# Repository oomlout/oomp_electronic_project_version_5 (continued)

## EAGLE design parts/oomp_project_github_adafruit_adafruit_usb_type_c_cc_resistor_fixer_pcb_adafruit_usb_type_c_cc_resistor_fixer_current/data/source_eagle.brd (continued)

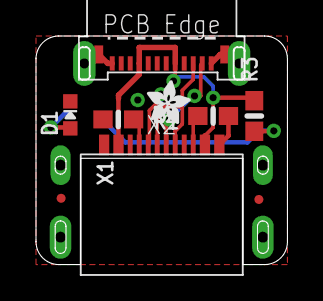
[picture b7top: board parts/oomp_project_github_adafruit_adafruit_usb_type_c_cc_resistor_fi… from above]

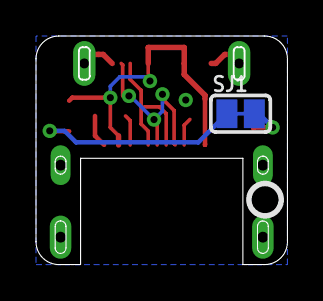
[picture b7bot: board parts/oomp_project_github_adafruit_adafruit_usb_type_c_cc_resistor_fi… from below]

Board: 2 copper layers, 14.0 x 12.7 mm, 14 parts (3 on the bottom side), 8 nets.

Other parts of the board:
PLABEL0: PLABEL0
PLABEL1: PLABEL1
PLABEL2: PLABEL2
U$3: ADAFRUIT_2.5MM
U$8: PCBFEAT-REV-040

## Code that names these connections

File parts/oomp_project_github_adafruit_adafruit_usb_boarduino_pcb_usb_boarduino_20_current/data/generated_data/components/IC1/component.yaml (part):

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    dnp: false
    pins:
    - number: '1'
      name: PC6(/RESET/PCI14)
      electrical_type: bidirectional
      graphic_style: inverted
      local_position:
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        pin_number: A'
        pin_name: P1
    - number: '2'
      name: (PCI16/RXD)PD0
      electrical_type: bidirectional
      graphic_style: line
      local_position:
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        pin_number: '1'
        pin_name: '1'
    - number: '3'
      name: (PCI17/TXD)PD1
      electrical_type: bidirectional
      graphic_style: line
      local_position:
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        pin_number: '2'
        pin_name: '2'
    - number: '4'
      name: (PCI18/INT0)PD2
      electrical_type: bidirectional
      graphic_style: line
      local_position:
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        pin_number: '3'
        pin_name: '3'
    - number: '5'
      name: (PCI19/INT1/OC2B)PD3
      electrical_type: bidirectional
      graphic_style: line
      local_position:
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        pin_number: '4'
        pin_name: '4'
    - number: '6'
      name: (PCI20/XCK/T0)PD4
      electrical_type: bidirectional
      graphic_style: line
      local_position:
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        pin_name: +
      - reference: IC1
        pin_number: '20'
        pin_name: AVCC
      - reference: IC2
        pin_number: '4'
        pin_name: VCCIO
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        pin_name: C
      - reference: IC1
        pin_number: '22'
        pin_name: AGND
      - reference: IC2
        pin_number: '7'
        pin_name: GND
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        pin_name: GND3
      - reference: IC2
        pin_number: '25'
        pin_name: AGND
      - reference: IC2
        pin_number: '26'
        pin_name: TEST
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        pin_number: GND
        pin_name: GND
    - number: '9'
      name: PB6(XTAL1/TOSC1/PCI6)
      electrical_type: bidirectional
      graphic_style: line
      local_position:
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        pin_number: P$2
        pin_name: P$2
    - number: '10'
      name: PB7(XTAL2/TOSC2/PCI7)
      electrical_type: bidirectional
      graphic_style: line
      local_position:
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        pin_number: P$1
        pin_name: P$1
    - number: '11'
      name: (PCI21/T1/OC0B)PD5
      electrical_type: bidirectional
      graphic_style: line
      local_position:
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        pin_number: '6'
        pin_name: '6'
    - number: '12'
      name: (PCI22/AIN0OC0A)PD6
      electrical_type: bidirectional
      graphic_style: line
      local_position:
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        pin_number: '7'
        pin_name: '7'
    - number: '13'
      name: (PCI23/AIN1)PD7
      electrical_type: bidirectional
      graphic_style: line
      local_position:
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        pin_number: '8'
        pin_name: '8'
    - number: '14'
      name: (PCI0/ICP/CLKO)PB0
      electrical_type: bidirectional
      graphic_style: line
      local_position:
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        pin_number: '1'
        pin_name: '1'
    - number: '15'
      name: (PCI1/OC1A/OC1S)PB1
      electrical_type: bidirectional
      graphic_style: line
      local_position:
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        pin_number: '2'
        pin_name: '2'
    - number: '16'
      name: (PCI2/SS/OC1B)PB2
      electrical_type: bidirectional
      graphic_style: line
      local_position:
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        pin_number: '3'
        pin_name: '3'
    - number: '17'
      name: (PCI3/MOSI/OC2A)PB3
      electrical_type: bidirectional
      graphic_style: line
      local_position:
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        pin_number: '4'
        pin_name: '4'
    - number: '18'
      name: (PCI4/MISO)PB4
      electrical_type: bidirectional
      graphic_style: line
      local_position:
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        pin_number: '1'
        pin_name: '1'
    - number: '19'
      name: (PCI5/SCK)PB5
      electrical_type: bidirectional
      graphic_style: line
      local_position:
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        pin_name: GND3
      - reference: IC2
        pin_number: '25'
        pin_name: AGND
      - reference: IC2
        pin_number: '26'
        pin_name: TEST
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        pin_number: GND
        pin_name: GND
    - number: '23'
      name: (PCI8/ADC0)PC0
      electrical_type: bidirectional
      graphic_style: line
      local_position:
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        pin_number: '1'
        pin_name: '1'
    - number: '24'
      name: (PCI9/ADC1)PC1
      electrical_type: bidirectional
      graphic_style: line
      local_position:
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        pin_number: '2'
        pin_name: '2'
    - number: '25'
      name: (PCI10/ADC2)PC2
      electrical_type: bidirectional
      graphic_style: line
      local_position:
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        pin_number: '3'
        pin_name: '3'
    - number: '26'
      name: (PCI11/ADC3)PC3
      electrical_type: bidirectional
      graphic_style: line
      local_position:
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        pin_number: '4'
        pin_name: '4'
    - number: '27'
      name: (PCI12/ADC4/SDA)PC4
      electrical_type: bidirectional
      graphic_style: line
      local_position:
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        pin_number: '5'
        pin_name: '5'
    - number: '28'
      name: (PCI13/ADC5/SCL)PC5
      electrical_type: bidirectional
      graphic_style: line
      local_position:
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    pin_name: C
  - reference: IC1
    pin_number: '20'
    pin_name: AVCC
  - reference: IC1
    pin_number: '22'
    pin_name: AGND
  - reference: IC1
    pin_number: '7'
    pin_name: VCC
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    pin_name: GND3
  - reference: IC2
    pin_number: '25'
    pin_name: AGND
  - reference: IC2
    pin_number: '26'
    pin_name: TEST
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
